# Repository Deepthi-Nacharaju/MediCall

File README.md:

# MediCall

## Directory of Repository

| Subject                                 | Folder            | File Name                                                                      | Objectives      |
|-----------------------------------------|-------------------|--------------------------------------------------------------------------------|-----------------|
| Project Organization Strategies         | General           | ProjectOrganization.pdf                                                        |                 |
| Old Design Foundations Document         | Cycle_One         | 10_11_18 Design Foundations Document (DFD).docx                                |                 |
| Medical Device Development Worksheet    | Cycle_One         | HaerynLizDeepthi_Medical Device Development Worksheet 2018.xlsx                |                 |
| Updated Design Foundation Document      | Cycle_Two         | Updated Design Foundations Document (DFD).pdf                                                               |                 |
| Updated Spec Sheet PDF                  | Cycle_Two         | HOQ and Specs.pdf                                                              |                 |
| Cycle 2 Presentation                    | Presentations     | Final_Presentation.pptx                                                        |                 |
| Functional Decompositions               | Cycle_Two         | FunctionalDecomposition.pdf                                                    | Objective 1     |
| Pugh Matrix for Patient Alert Mechanism | Cycle_Two         | Scoring_User_Alert.xlsx                                                        | Objective 2     |
| Pugh Matrix for Nurse Alert Mechanism   | Cycle_Two         | Scoring_Alert.xlsx                                                             | Objective 3     |
| Pugh Matrix for Sensing Mechanism       | Cycle_Two         | Scoring_Sensor.xlsx                                                            | Objective 4     |
| +/- List for Battery v. Wall Power      | Cycle_Two         | BatteryvsMains.xlsx                                                            | Objective 5     |
| Pugh Matrix for Battery Type            | Cycle_Two         | Scoring_Battery.xlsx                                                           |                 |
| Hospital Policy on Bluetooth and Wifi   | Cycle_Two         | Bluetooth vs. Wifi Regulation Research.pdf                                     | Objective 6     |
| Sketch of System                        | Cycle_Two         | sketchofsystem.pdf                                                             | Objective 7     |
| Mechanical CAD of System                | Mechanical        | sensor.SLDPRT; sensor holder.SLDPRT; clamp.SLDPRT; strokesensorassembly.SLDASM | Objective 7     |
| Software Code Block Diagram             | Cycle_Two         | codeblockdiagram.pdf                                                           | Objective 8     |
| Demo Video of Prototype                 | Data              | IMG_7550.MOV                                                                   | Objective 9, 10 |
| List of System Components               | General           | Materials .xlsx                                                                |                 |
| Patient Flow Chart                      | Problem Statement | Patient flow-chart.pdf                                                         |                 |
|Updated Design Foundations Documentation| Cycle_Two| Updated Design Foundations Documentation. pdf

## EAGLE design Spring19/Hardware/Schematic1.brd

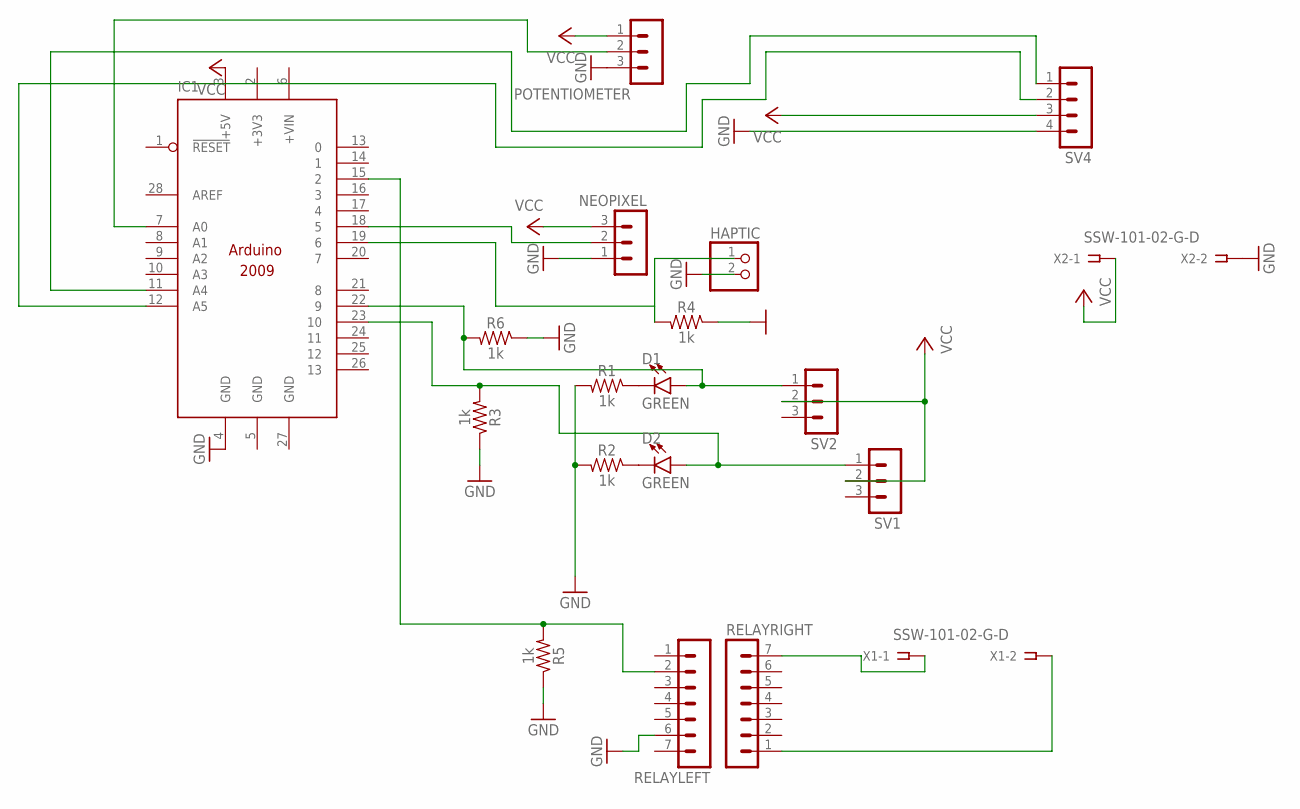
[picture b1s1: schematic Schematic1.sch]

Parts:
D1, D2: GREEN; LED-1206
HAPTIC: PINHD-1X2; 1X02
IC1: ARDUINO2009_10; ARDUINO2009
NEOPIXEL: MA03-1
POTENTIOMETER: MA03-1
R1, R2, R3, R4, R5, R6: 1k; 0603
RELAYLEFT: MA07-1
RELAYRIGHT: MA07-1
SV1, SV2: MA03-1
SV4: MA04-1
X1, X2: SSW-101-02-G-D

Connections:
+3V3: IC1.2 (+3V3)
GND: HAPTIC.2, IC1.4 (GND), IC1.5 (GND), IC1.27 (GND), NEOPIXEL.1, POTENTIOMETER.3, R1.2, R2.2, R3.1, R4.1, R5.1, R6.1, RELAYLEFT.6, SV4.4, X2.2
unnamed: D1.C, R1.1
unnamed: D2.C, R2.1
unnamed: D2.A, IC1.23 (10), R3.2, SV1.1
unnamed: D1.A, IC1.22 (9), R6.2, SV2.1
unnamed: IC1.18 (5), NEOPIXEL.2
unnamed: IC1.11 (A4), SV4.1
unnamed: IC1.12 (A5), SV4.2
unnamed: HAPTIC.1, IC1.19 (6), R4.2
unnamed: RELAYRIGHT.7, X1.1
unnamed: IC1.7 (A0), POTENTIOMETER.2
unnamed: RELAYRIGHT.1, X1.2
unnamed: IC1.15 (2), R5.2, RELAYLEFT.2
VCC: IC1.3 (+5V), NEOPIXEL.3, POTENTIOMETER.1, SV1.2, SV2.2, SV4.3, X2.1

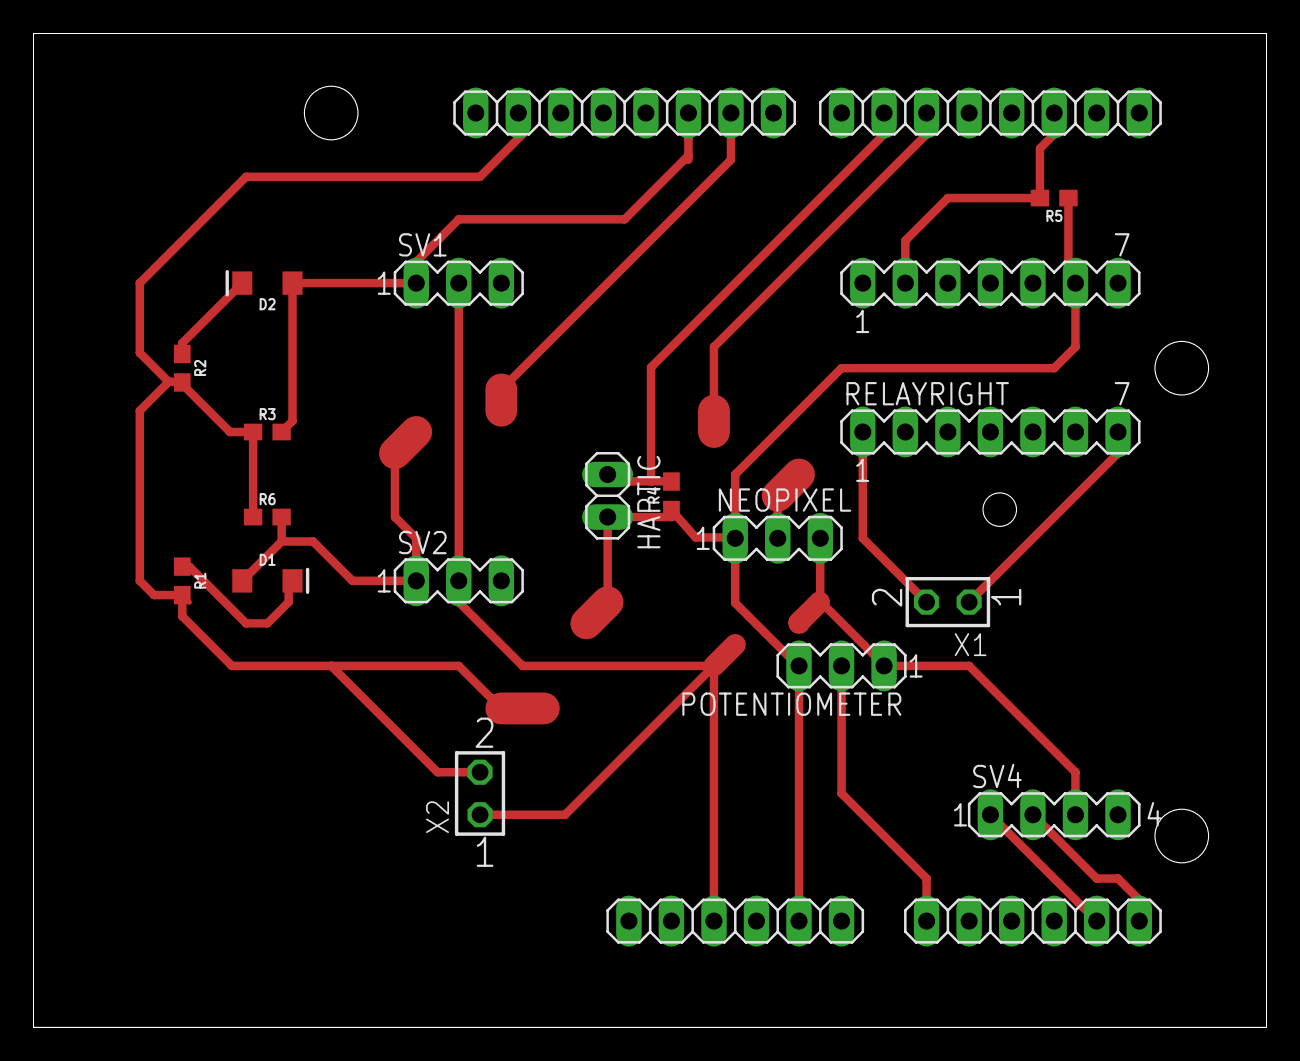
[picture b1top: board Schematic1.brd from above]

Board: 2 copper layers, 73.6 x 59.4 mm, 19 parts (0 on the bottom side), 14 nets.

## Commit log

2018-11-27 Add all documents from google drive
2018-11-28 Initial CAD designs
2018-12-01 Add code block diagram slide
2018-12-01 Pugh Matrices
2018-12-02 Add testing plan
2018-12-02 Adjust cell widths
2018-12-02 Create final presentation skeleton
2018-12-02 Add objectives slide
2018-12-03 Add Device Powering Mechanism Pugh Matrix in addition to pro-con list
2018-12-03 Add lots of stuff to the slides
2018-12-03 Working draft of Bluetooth v Wifi regulations research (Addresses #6)
2018-12-05 Revise and finish Bluetooth v Wifi Regulation Document
2018-12-05 Add to final presentation
2018-12-05 add solidworks screenshot
2018-12-06 Project Management
2018-12-06 Add BT v Wifi regulations to slide deck
2018-12-07 Add rechargeable battery options
2018-12-07 Add citations and PDF version of regulations research
2018-12-07 Update slides with bluetooth research
2018-12-07 Add pdf of Project Organization paragraph
2018-12-07 Add sketch and functional decomposition of device
2018-12-07 Fix errors on BT research slides
2018-12-07 Add excel sheet pdf
2018-12-07 adjust specs
2018-12-07 Save submitted HOQ
2018-12-07 Add pdf of updated objectives
2018-12-07 Reorder slides according to objective numbering
2018-12-07 Add directory of current repository
2018-12-07 Add old slide with three parts of prototype
2018-12-07 Edit presentation layout
2018-12-07 Final_Presentation.pptx add updated design
2019-01-21 Add Jack Research
2019-01-21 Add setup image from 1 21 19
2019-01-25 Add Arduino code that connects IR sensor to LEDs
2019-01-27 Working light code
2019-02-21 Update software 2_12_2019
2019-02-22 Added code from the DFPlayer test code that worked on feb 21
2019-02-25 stash
2019-02-25 Add df player code
2019-02-25 Working EAGLE schematic
2019-02-27 Upload Medicall_2_26.ino
    This is the code uploaded to the microchip prior to removal from the Uno.
2019-03-04 Add code to test relay
2019-03-05 Add datasheet and pinout map of relay
2019-03-11 Updated schematic with arduino shield
2019-03-12 Attempt 1 at routing
2019-03-18 Finish routing
2019-03-18 Add through holes for plug
2019-03-19 Single sided board with airwires
2019-03-19 Fix relay width
2019-03-19 Adjst trace widths
2019-03-19 Adjust wonky routes
2019-03-20 Adjust cap1188 footprint and add some bottom routes
2019-03-20 Adjust routes
2019-03-20 airwire route thickness
2019-03-20 Switch back to airwires; single sided boards
2019-03-20 adjust routes again
2019-03-27 PCB for etching
2019-03-28 Switch relay direction
2019-04-04 for etching 4.3.19
2019-04-10 Nano code
2019-04-14 Add hazard analysis report
2019-04-17 Add Parts List
2019-04-17 Update with total cost
2019-04-17 Add Semester Parts List
2019-04-18 Add files via upload
    TO PRINT
2019-04-22 add power supply hole
2019-04-22 Add files via upload
    Adjust hole size for threaded inserts
2019-04-22 Add files via upload
    sensor top changes
2019-04-25 Add pdfs of drawings
2019-04-30 Add customer satisfaction survey
    Necessary device evaluation component
2019-05-01 Add Solidworks CAD drawings with dimensions
2019-05-03 Add editable CAD files etc in Appendix E

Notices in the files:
parts and their libraries:
SparkFun-LED: Licensing: Creative Commons ShareAlike 4.0 International - https://creativecommons.org/licenses/by-sa/4.0
